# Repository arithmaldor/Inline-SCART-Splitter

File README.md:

# Inline SCART Splitter
Split a SCART signal in 2 in as little space as possible.

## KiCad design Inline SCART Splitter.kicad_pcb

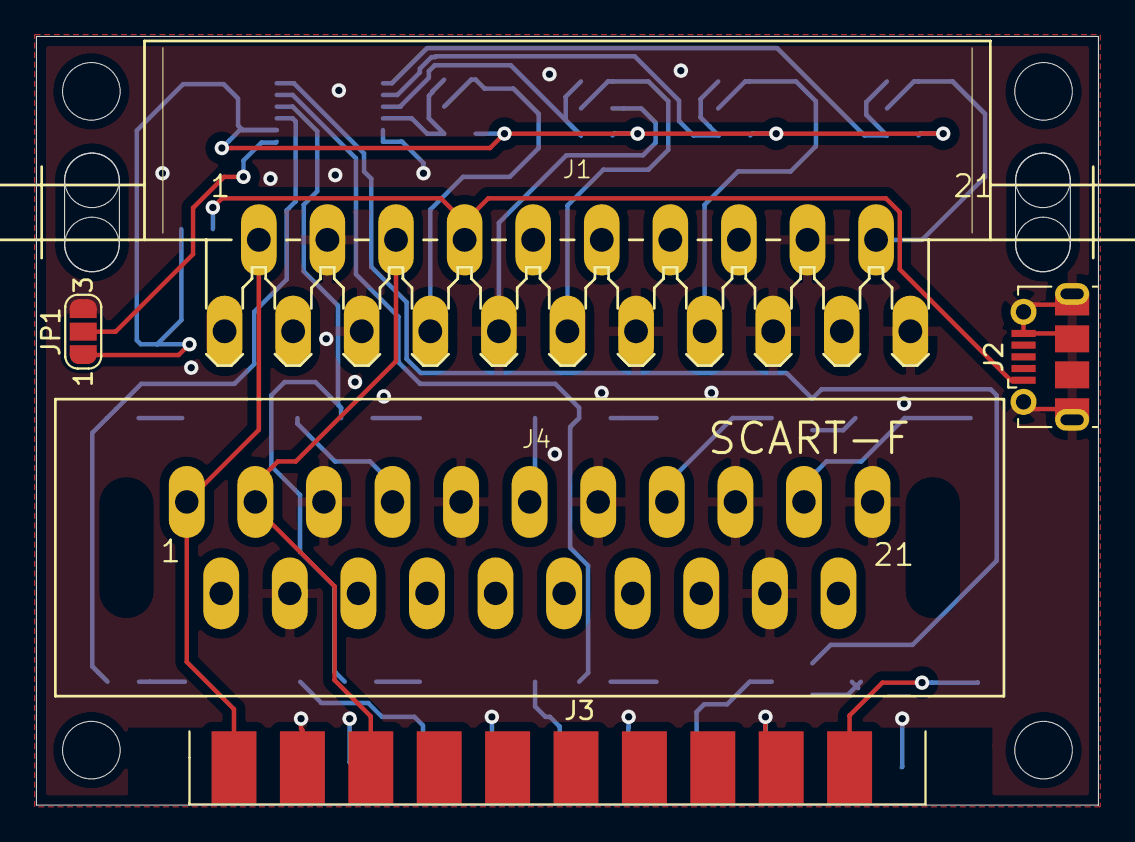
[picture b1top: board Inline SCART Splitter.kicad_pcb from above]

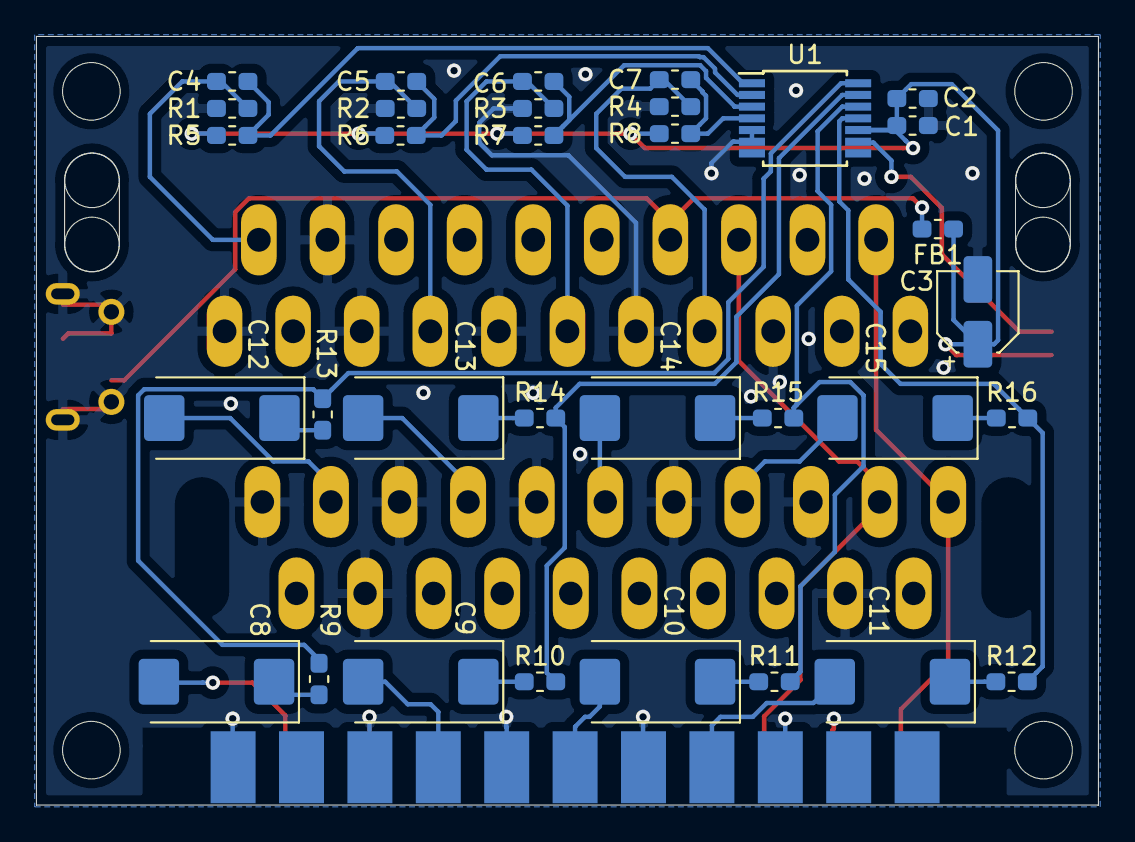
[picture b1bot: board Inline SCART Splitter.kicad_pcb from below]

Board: 2 copper layers, 59.0 x 42.7 mm, 38 parts (33 on the bottom side), 34 nets.

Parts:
C1: 10nF; C_0603_1608Metric_Pad1.05x0.95mm_HandSolder
C2, C4, C5, C6, C7: 100nF; C_0603_1608Metric_Pad1.05x0.95mm_HandSolder
C3: 10uF; CP_Elec_4x5.4
C8, C9, C10, C11, C12, C13, C14, C15: 220uF; CP_EIA-7343-30_AVX-N_Pad2.25x2.55mm_HandSolder
FB1: 220; L_0603_1608Metric_Pad1.05x0.95mm_HandSolder
J1: SCART-F; SCART-F-RA
J2: USB_B_Micro; USB_Micro-B_Molex-105017-0001
J3: SCART-F; MALE_SCART
J4: SCART-F; SCART_F_VERT
JP1: SolderJumper_3_Bridged12; SolderJumper-3_P1.3mm_Open_RoundedPad1.0x1.5mm_NumberLabels
R1, R2, R3, R4, R9, R10, R11, R12, R13, R14, R15, R16: 75; R_0603_1608Metric_Pad1.05x0.95mm_HandSolder
R5, R6, R7, R8: 5.6M; R_0603_1608Metric_Pad1.05x0.95mm_HandSolder
U1: THS7374; TSSOP-14_4.4x5mm_P0.65mm

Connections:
5V: C1.1, C2.1, C3.1, FB1.1, JP1.1, R5.2, R6.2, R7.2, R8.2, U1.10
BLUE_IN: C7.2, J1.7, R4.2
BYPASS: JP1.2, U1.9
GND: C1.2, C2.2, C3.2, J1.4, J1.5, J1.9, J1.13, J1.17, J1.18, J1.21, J2.5, J2.6, J3.4, J3.5, J3.9, J3.13, J3.17, J3.18, J3.21, J4.4, J4.5, J4.9, J4.13, J4.17, J4.18, J4.21, JP1.3, R1.1, R2.1, R3.1, R4.1, U1.5, U1.6
GREEN_IN: C6.2, J1.11, R3.2
LEFT: J1.6, J3.6, J4.3
unnamed: C4.1, R5.1, U1.1
unnamed: C5.1, R6.1, U1.2
unnamed: C6.1, R7.1, U1.3
unnamed: C7.1, R8.1, U1.4
unnamed: C8.1, R9.1
unnamed: C8.2, J3.20
unnamed: C9.1, R10.1
unnamed: C9.2, J3.15
unnamed: C10.1, R11.1
unnamed: C10.2, J3.11
unnamed: C11.1, R12.1
unnamed: C11.2, J3.7
unnamed: C12.1, R13.1
unnamed: C12.2, J4.19
unnamed: C13.1, R14.1
unnamed: C13.2, J4.15
unnamed: C14.1, R15.1
unnamed: C14.2, J4.11
unnamed: C15.1, R16.1
unnamed: C15.2, J4.7
unnamed: FB1.2, J1.8, J2.1
unnamed: R10.2, R14.2, U1.13
unnamed: R11.2, R15.2, U1.12
unnamed: R12.2, R16.2, U1.11
unnamed: R9.2, R13.2, U1.14
RED_IN: C5.2, J1.15, R2.2
RIGHT: J1.2, J3.2, J4.1
SYNC_IN: C4.2, J1.20, R1.2

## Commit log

2019-06-26 Finished board, added renders
2019-07-10 generated gerbers
2019-07-31 Small corrections after first fab
    fixed C2 silkscreen, removed SCART footprint from paste layers
2019-07-31 exported footprints
